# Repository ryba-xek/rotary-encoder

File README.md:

# rotation-sensor
Multipole AS5047D motor shaft sensor emulating standard UVW hall effect sensor signals

Please note, that AS5047d position is shifted by 1mm from the center of the board.

Emulates Hall sensors UVW signals for 14-pole BLDC motor.

## Building
`platformio run -e ATMEGA328P`

## Flashing
This code is supposed to be uploaded via standard AVR ISP programmer.
Please set fuses to `L=0xF7 H=0xD9 E=0xFF`

`avrdude -c usbasp -p m328p -P usb -e -U lfuse:w:0xF7:m -U hfuse:w:0xD9:m -U efuse:w:0xFF:m`

http://eleccelerator.com/fusecalc/fusecalc.php?chip=atmega328p&LOW=F7&HIGH=D9&EXTENDED=FF&LOCKBIT=FF

upload with `platformio run -t program -e ATMEGA328P`

## Testing
`platformio test -e native`

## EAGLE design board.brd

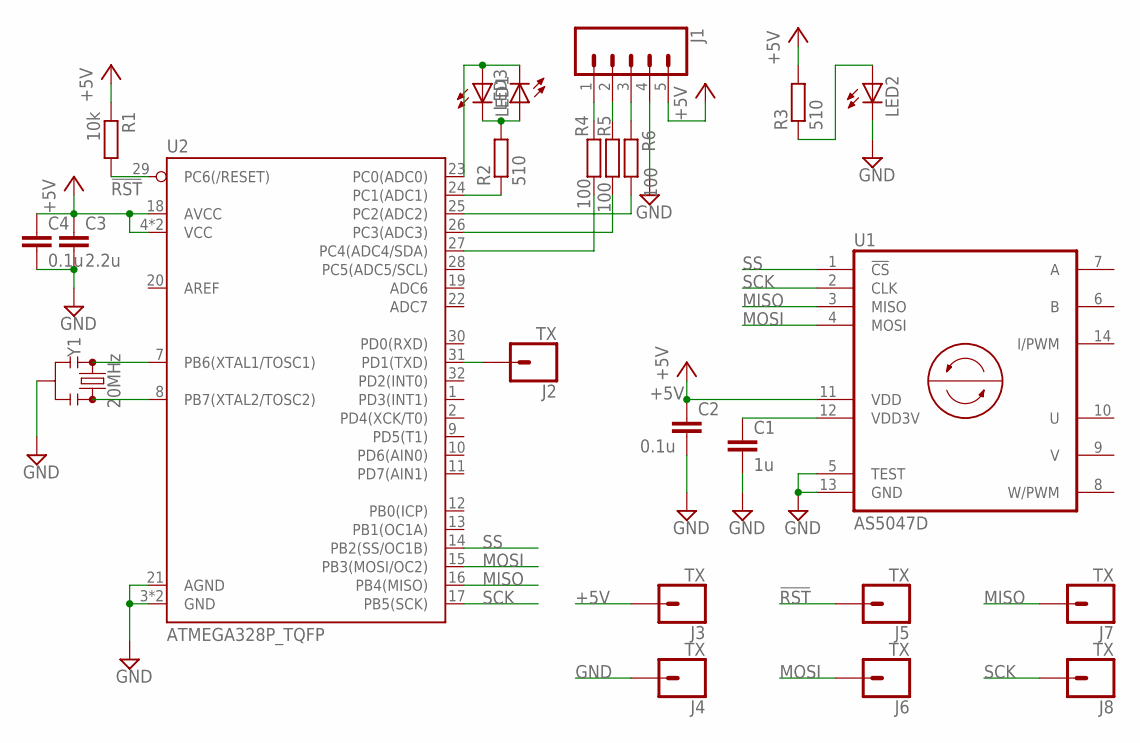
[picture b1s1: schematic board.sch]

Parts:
C1: 1u; C0603
C2, C4: 0.1u; C0603
C3: 2.2u; C0603
J1: CONN_05PTH_LONGPADS; 1X05_LONGPADS
J2, J3, J4, J5, J6, J7, J8: TX; 1X01_NO_SILK
LED1, LED2, LED3: LEDSML0805; SML0805
R1: 10k; R0603
R2, R3: 510; R0603
R4, R5, R6: 100; R0603
U1: AS5047D; TSSOP14
U2: ATMEGA328P_TQFP; TQFP32-08
Y1: 20MHz; CSTCE20M0V53-R0

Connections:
!RST: J5.1, R1.2, U2.29 (PC6(/RESET))
+5V: C2.1, C3.1, C4.1, J1.5, J3.1, R1.1, R3.2, U1.11 (VDD), U2.4 (VCC), U2.6 (VCC), U2.18 (AVCC)
GND: C1.2, C2.2, C3.2, C4.2, J1.4, J4.1, LED2.C, U1.5 (TEST), U1.13 (GND), U2.3 (GND), U2.5 (GND), U2.21 (AGND), Y1.2
MISO: J7.1, U1.3 (MISO), U2.16 (PB4(MISO))
MOSI: J6.1, U1.4 (MOSI), U2.15 (PB3(MOSI/OC2))
unnamed: U2.7 (PB6(XTAL1/TOSC1)), Y1.1
unnamed: U2.8 (PB7(XTAL2/TOSC2)), Y1.3
unnamed: R6.2, U2.25 (PC2(ADC2))
unnamed: R4.2, U2.27 (PC4(ADC4/SDA))
unnamed: R5.2, U2.26 (PC3(ADC3))
unnamed: LED1.A, LED3.C, U2.23 (PC0(ADC0))
unnamed: J1.1, R4.1
unnamed: LED2.A, R3.1
unnamed: J2.1, U2.31 (PD1(TXD))
unnamed: J1.2, R5.1
unnamed: R2.1, U2.24 (PC1(ADC1))
unnamed: LED1.C, LED3.A, R2.2
unnamed: J1.3, R6.1
SCK: J8.1, U1.2 (CLK), U2.17 (PB5(SCK))
SS: U1.1 (!CS!), U2.14 (PB2(SS/OC1B))
VDD3V: C1.1, U1.12 (VDD3V)

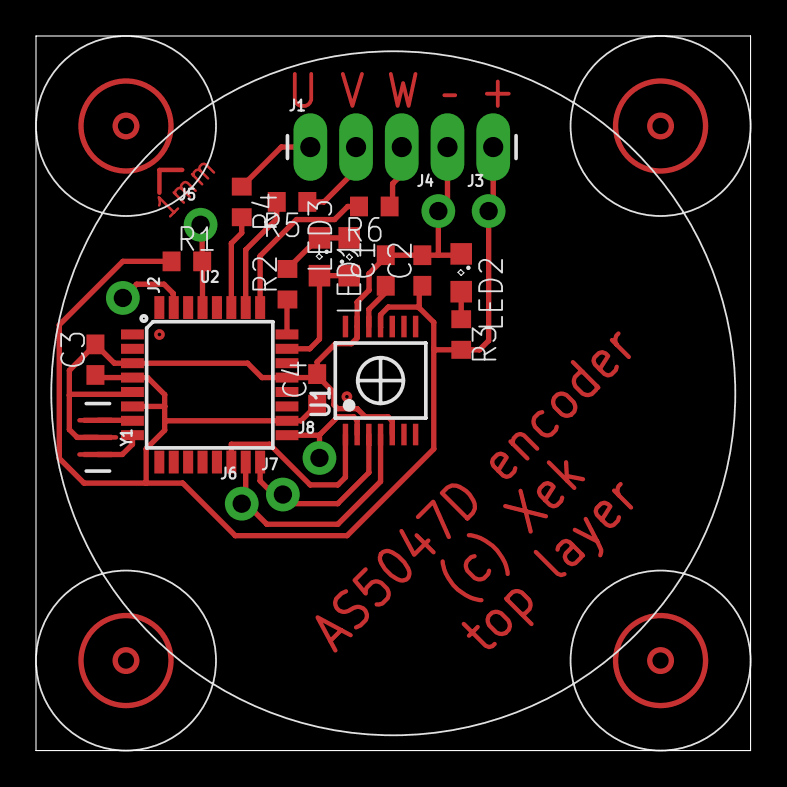
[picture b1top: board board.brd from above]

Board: 2 copper layers, 39.7 x 39.7 mm, 24 parts (0 on the bottom side), 21 nets.

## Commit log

2019-07-07 board v1
2019-07-08 Board v2
2019-07-15 Alpha version for 14-pole motor
2019-07-17 Bugs fixed Unit tests
2019-07-17 Better readme, more tests
2019-07-17 Bug fixed, more tests

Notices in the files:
parts and their libraries:
ams: Copyright (C) 2015, Bob Starr
SparkFun-IC-Microcontroller: Licensing: Creative Commons ShareAlike 4.0 International - https://creativecommons.org/licenses/by-sa/4.0
